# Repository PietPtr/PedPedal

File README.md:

# Footswitches

A modular USB MIDI footswitch controller. Each module is one PCB with a footswitch and an RGB
LED, and modules chain together with ribbon cables. The first module carries a Raspberry Pi
Pico, which is the USB MIDI device. All parts are through-hole. Firmware and host tools are in Rust.

- [docs/build.md](docs/build.md) ([PDF](docs/build.pdf)): build instructions
- [docs/design.md](docs/design.md): board and enclosure design
- [docs/bom.md](docs/bom.md): parts list
- [docs/firmware.md](docs/firmware.md): firmware, config libraries (Rust, Python, JS), the `fsctl` tool and the browser config page
- `pcb/`: KiCad project. `mech/`: plates, walls and 3D assembly. `firmware/`, `driver/`, `core/`: Rust code. `driver-py/`, `driver-js/`: Python and JS config libraries. `site/`: product page and config page.

--- 

Basically all of this is AI generated. Let's see if this thing actually works.

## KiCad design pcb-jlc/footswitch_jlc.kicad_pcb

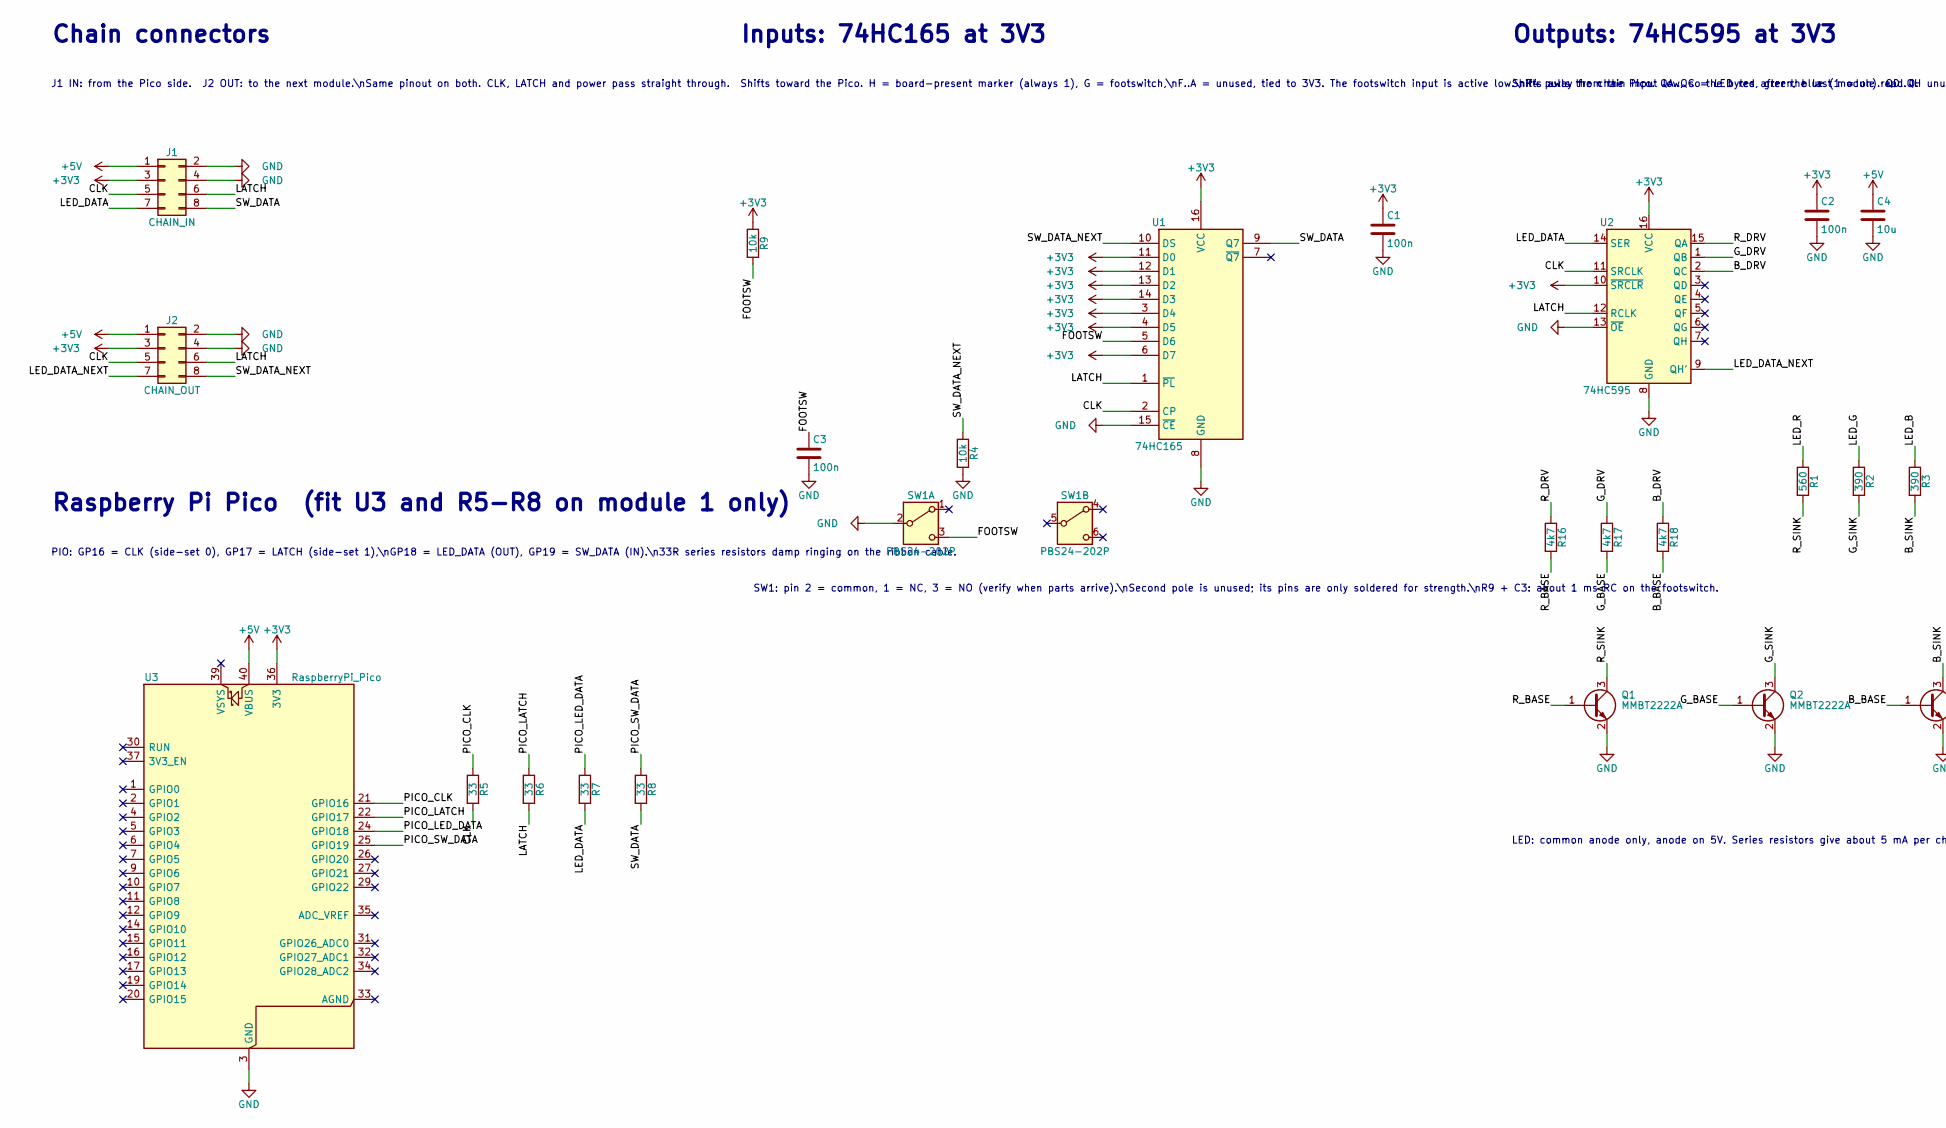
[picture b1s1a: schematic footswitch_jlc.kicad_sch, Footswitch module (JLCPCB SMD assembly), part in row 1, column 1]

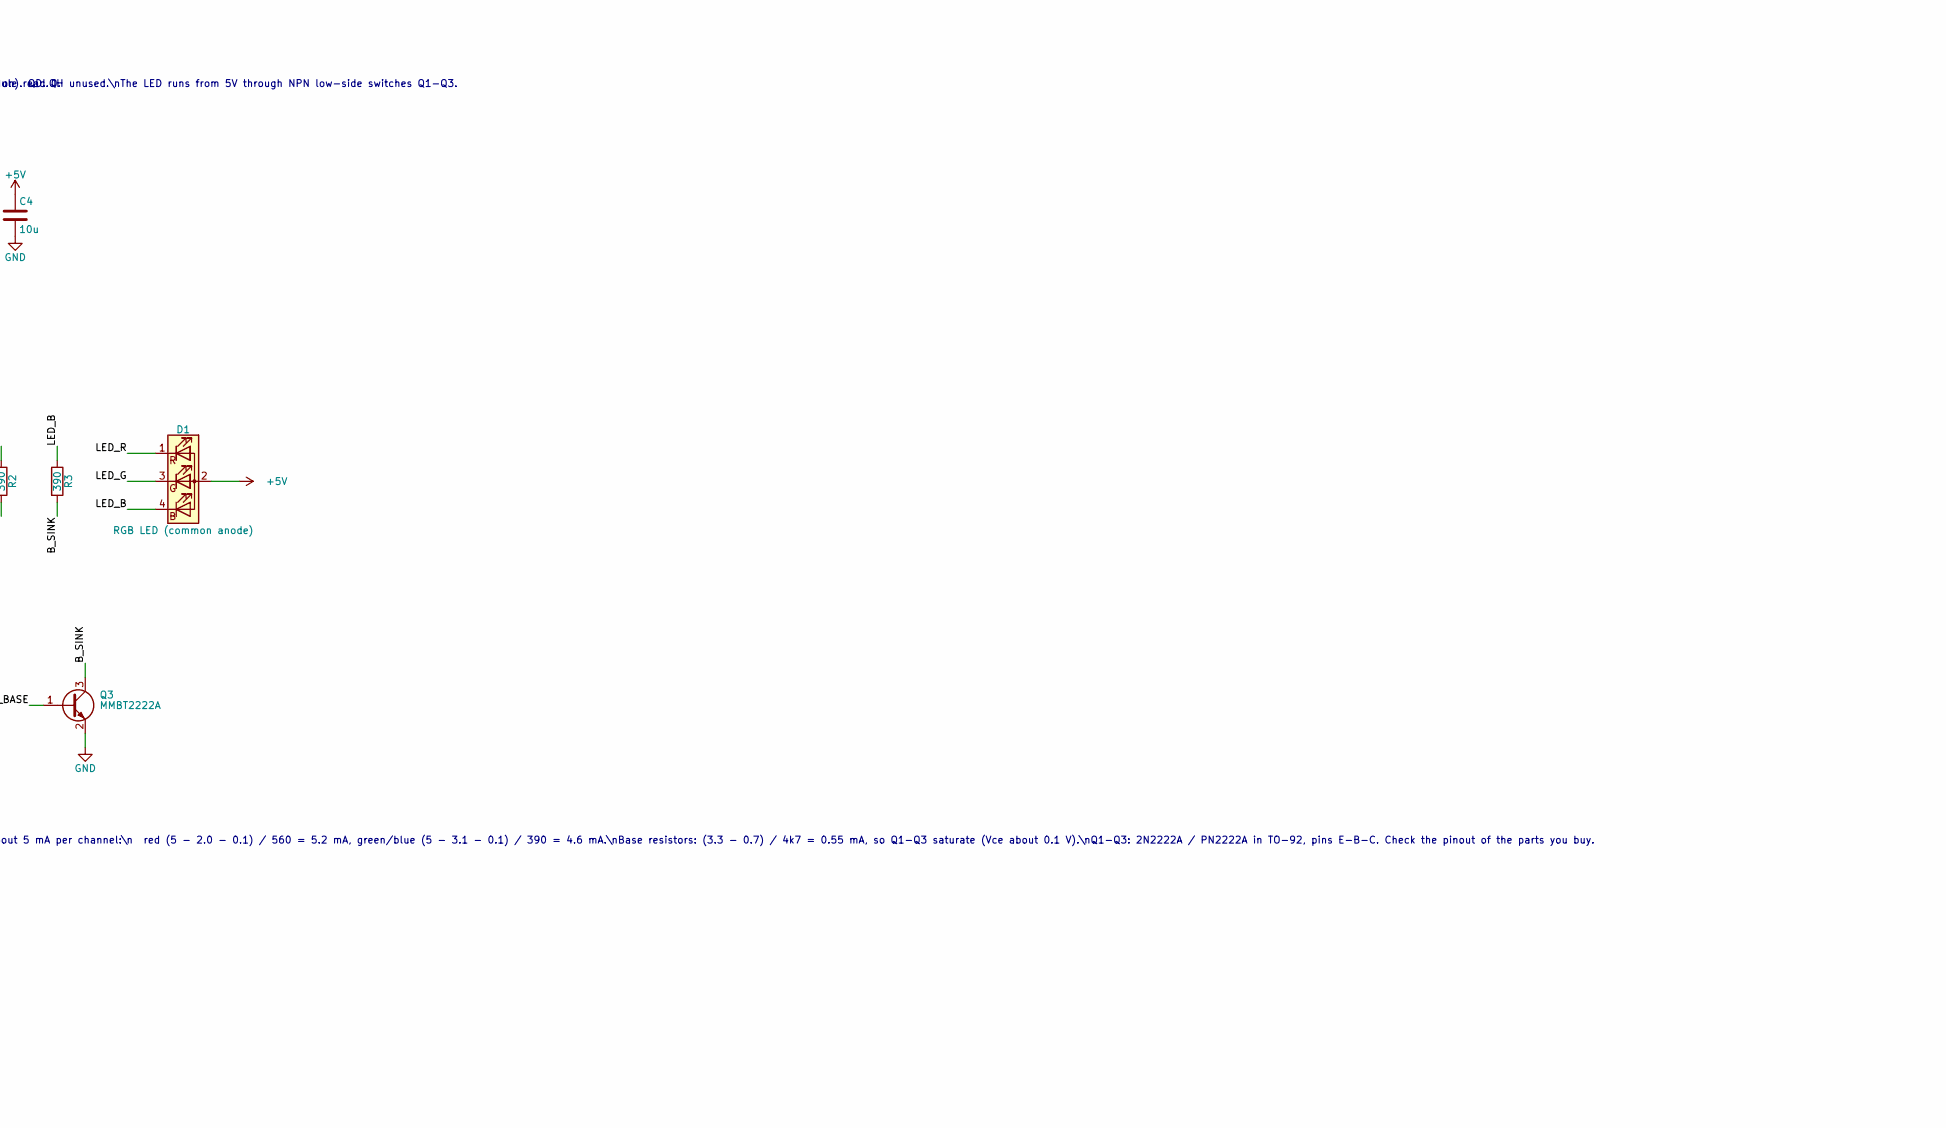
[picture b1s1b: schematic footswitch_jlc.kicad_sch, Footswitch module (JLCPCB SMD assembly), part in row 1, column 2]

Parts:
C1, C2, C3: 100n; C_0805_2012Metric; LCSC C49678
C4: 10u; C_0805_2012Metric; LCSC C15850
D1: RGB LED (common anode); LED_D5.0mm-4_RGB_Staggered_Pins
J1: CHAIN_IN; IDC-Header_2x04_P2.54mm_Vertical_SMD_JLC; LCSC C56143593
J2: CHAIN_OUT; IDC-Header_2x04_P2.54mm_Vertical_SMD_JLC; LCSC C56143593
Q1, Q2, Q3: MMBT2222A; SOT-23; LCSC C8512
R1: 560; R_0805_2012Metric; LCSC C28636
R2, R3: 390; R_0805_2012Metric; LCSC C17655
R4, R9: 10k; R_0805_2012Metric; LCSC C17414
R5, R6, R7, R8: 33; R_0805_2012Metric; LCSC C17634
R16, R17, R18: 4k7; R_0805_2012Metric; LCSC C17673
SW1: PBS24-202P
U1: 74HC165; SOIC-16_3.9x9.9mm_P1.27mm; LCSC C5613
U2: 74HC595; SOIC-16_3.9x9.9mm_P1.27mm; LCSC C5947
U3: RaspberryPi_Pico; RaspberryPi_Pico_Common_THT

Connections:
+3V3: C1.1, C2.1, J1.3, J2.3, R9.1, U1.3 (D4), U1.4 (D5), U1.6 (D7), U1.11 (D0), U1.12 (D1), U1.13 (D2), U1.14 (D3), U1.16 (VCC), U2.10 (~SRCLR), U2.16 (VCC), U3.36 (3V3)
+5V: C4.1, D1.2 (A), J1.1, J2.1, U3.40 (VBUS)
/B_BASE: Q3.1 (B), R18.2
/B_DRV: R18.1, U2.2 (QC)
/B_SINK: Q3.3 (C), R3.2
/CLK: J1.5, J2.5, R5.2, U1.2 (CP), U2.11 (SRCLK)
/FOOTSW: C3.1, R9.2, SW1.3 (C), U1.5 (D6)
/G_BASE: Q2.1 (B), R17.2
/G_DRV: R17.1, U2.1 (QB)
/G_SINK: Q2.3 (C), R2.2
/LATCH: J1.6, J2.6, R6.2, U1.1 (~PL), U2.12 (RCLK)
/LED_B: D1.4 (BK), R3.1
/LED_DATA: J1.7, R7.2, U2.14 (SER)
/LED_DATA_NEXT: J2.7, U2.9 (QH')
/LED_G: D1.3 (GK), R2.1
/LED_R: D1.1 (RK), R1.1
/PICO_CLK: R5.1, U3.21 (GPIO16)
/PICO_LATCH: R6.1, U3.22 (GPIO17)
/PICO_LED_DATA: R7.1, U3.24 (GPIO18)
/PICO_SW_DATA: R8.1, U3.25 (GPIO19)
/R_BASE: Q1.1 (B), R16.2
/R_DRV: R16.1, U2.15 (QA)
/R_SINK: Q1.3 (C), R1.2
/SW_DATA: J1.8, R8.2, U1.9 (Q7)
/SW_DATA_NEXT: J2.8, R4.1, U1.10 (DS)
GND: C1.2, C2.2, C3.2, C4.2, J1.2, J1.4, J2.2, J2.4, Q1.2 (E), Q2.2 (E), Q3.2 (E), R4.2, SW1.2 (B), U1.8 (GND), U1.15 (~CE), U2.8 (GND), U2.13 (~OE), U3.3 (GND), U3.8 (GND), U3.13 (GND), U3.18 (GND), U3.23 (GND), U3.28 (GND), U3.38 (GND)

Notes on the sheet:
Chain connectors
J1 IN: from the Pico side. J2 OUT: to the next module.\nSame pinout on both. CLK, LATCH and power pass straight through.
Raspberry Pi Pico (fit U3 and R5-R8 on module 1 only)
PIO: GP16 = CLK (side-set 0), GP17 = LATCH (side-set 1),\nGP18 = LED_DATA (OUT), GP19 = SW_DATA (IN).\n33R series resistors damp ringing on the ribbon cable.
Inputs: 74HC165 at 3V3
Shifts toward the Pico. H = board-present marker (always 1), G = footswitch,\nF..A = unused, tied to 3V3. The footswitch input is active low.\nR4 pulls the chain input low, so the bytes after the last module read 0.
SW1: pin 2 = common, 1 = NC, 3 = NO (verify when parts arrive).\nSecond pole is unused; its pins are only soldered for strength.\nR9 + C3: about 1 ms RC on the footswitch.
Outputs: 74HC595 at 3V3
Shifts away from the Pico. QA..QC = LED red, green, blue (1 = on). QD..QH unused.\nThe LED runs from 5V through NPN low-side switches Q1-Q3.
LED: common anode only, anode on 5V. Series resistors give about 5 mA per channel:\n red (5 - 2.0 - 0.1) / 560 = 5.2 mA, green/blue (5 - 3.1 - 0.1) / 390 = 4.6 mA.\nBase resistors: (3.3 - 0.7) / 4k7 = 0.55 mA, so Q1-Q3 saturate (Vce about 0.1 V).\nQ1-Q3: 2N2222A / PN2222A in TO-92, pins E-B-C. Chec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

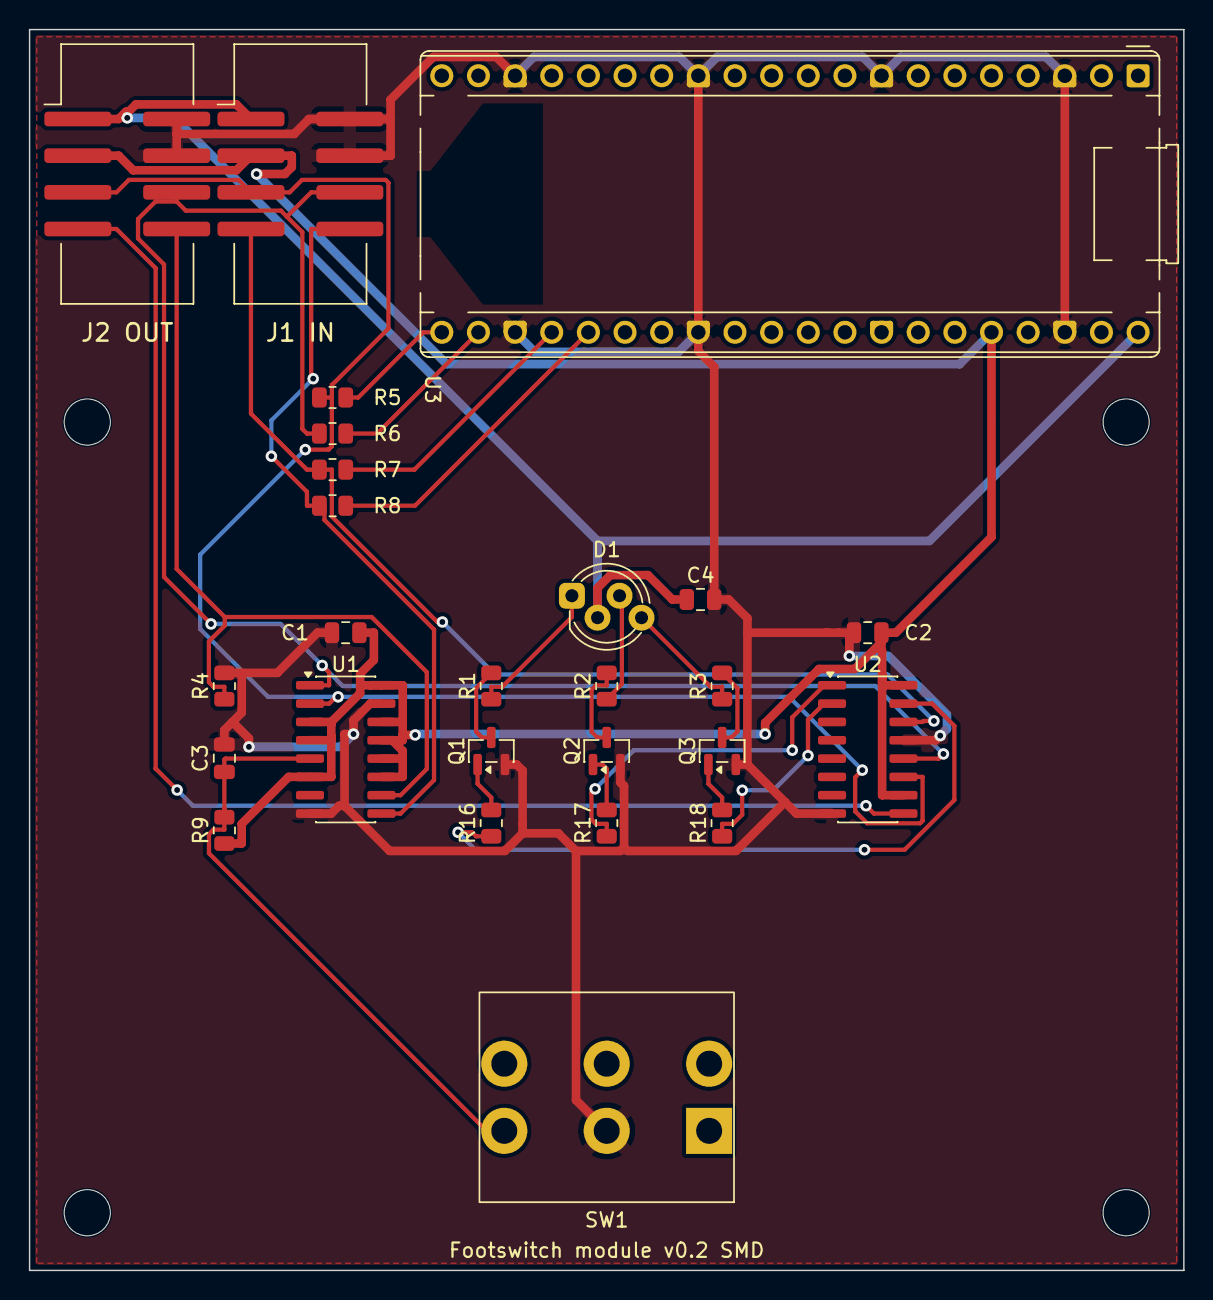
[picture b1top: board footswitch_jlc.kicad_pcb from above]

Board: 2 copper layers, 80.0 x 86.0 mm, 30 parts (0 on the bottom side), 26 nets.

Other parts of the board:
H1, H2, H3, H4: M3; MountingHole_3.2mm_M3

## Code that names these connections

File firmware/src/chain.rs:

//! Scans the module chain (74HC165 switch inputs, 74HC595 LED outputs) with PIO0.
//!
//! See docs/design.md, "Shift register bit assignment" and "Scan timing". One scan:
//!
//! 1. LATCH low: every 165 loads its inputs.
//! 2. LATCH high: every 595 copies what was shifted in during the previous scan to its outputs.
//! 3. 8 × MAX_PEDALS times: set LED_DATA, sample SW_DATA, pulse CLK high.
//!
//! The firmware always clocks MAX_PEDALS bytes, whatever the number of modules. Switch bytes
//! after the last module read 0 (the end-of-chain pull-down), which is how the module count is
//! found. LED bytes go out last module first, so the final bytes sent are the ones that stay in
//! the chain: whatever the chain length, module k ends up holding `leds[k]`.

use footswitch_core::MAX_PEDALS;
use rp2040_hal::gpio::{FunctionPio0, Pin, PullDown, PullNone, bank0};
use rp2040_hal::pac::{PIO0, RESETS};
use rp2040_hal::pio::{PIOBuilder, PIOExt, PinDir, Rx, SM0, ShiftDirection, Tx};

pub type ClkPin = Pin<bank0::Gpio16, FunctionPio0, PullNone>;
pub type LatchPin = Pin<bank0::Gpio17, FunctionPio0, PullNone>;
pub type LedDataPin = Pin<bank0::Gpio18, FunctionPio0, PullNone>;
pub type SwDataPin = Pin<bank0::Gpio19, FunctionPio0, PullDown>;

const CLK: u8 = 16; // side-set bit 0
const LATCH: u8 = 17; // side-set bit 1
const LED_DATA: u8 = 18; // OUT pin
const SW_DATA: u8 = 19; // IN pin

pub struct Chain {
    tx: Tx<(PIO0, SM0)>,
    rx: Rx<(PIO0, SM0)>,
    _pins: (ClkPin, LatchPin, LedDataPin, SwDataPin),
}

impl Chain {
    pub fn new(
        pio0: PIO0,
        resets: &mut RESETS,
        pins: (ClkPin, LatchPin, LedDataPin, SwDataPin),
    ) -> Self {
        // Side-set bits: 0 = CLK, 1 = LATCH. LATCH idles high, CLK idles low.
        // TX FIFO: first the byte count minus one, then one LED byte per word (in bits 31..24).
        // RX FIFO: one switch byte per word (bits 7..0, the first bit read in bit 7).
        let program = pio_proc::pio_asm!(
            ".side_set 2",
            ".wrap_target",
            "    pull block          side 0b10",     // byte count - 1
            "    mov y, osr          side 0b10",
            "    nop                 side 0b00 [7]", // LATCH low: 165s load
            "    nop                 side 0b10 [7]", // LATCH high: 595s update
            "byteloop:",
            "    pull block          side 0b10",     // next LED byte
            "    set x, 7            side 0b10",
            "bitloop:",
            "    out pins, 1         side 0b10 [1]", // LED_DATA
            "    in pins, 1          side 0b10 [1]", // sample SW_DATA
            "    jmp x-- bitloop     side 0b11 [2]", // CLK high: both chains shift
            "    push block          side 0b10",
            "    jmp y-- byteloop    side 0b10",
            ".wrap",
        );

        let (mut pio, sm0, _, _, _) = pio0.split(resets);
        let installed = pio.install(&program.program).unwrap();
        // 125 MHz / 31.25 = 4 MHz PIO clock. A bit takes 7 PIO cycles, so CLK runs at about
        // 570 kHz: slow, for margin on long ribbon chains. 16 modules scan in about 250 µs.
        let (mut sm, rx, tx) = PIOBuilder::from_installed_program(installed)
            .side_set_pin_base(CLK)
            .out_pins(LED_DATA, 1)
            .in_pin_base(SW_DATA)
            .out_shift_direction(ShiftDirection::Left)
            .in_shift_direction(ShiftDirection::Left)
            .autopull(false)
            .autopush(false)
            .clock_divisor_fixed_point(31, 64)
            .build(sm0);
        sm.set_pindirs([
            (CLK, PinDir::Output),
            (LATCH, PinDir::Output),
            (LED_DATA, PinDir::Output),
            (SW_DATA, PinDir::Input),
        ]);
        sm.start();
        // Dropping `pio` here is fine: the state machine and its program keep running.

        Chain { tx, rx, _pins: pins }
    }

    /// Runs one scan: shows `leds` (module 1 first; bit 0 red, 1 green, 2 blue) after the next
    /// latch, and returns the switch bytes read (module 1 first).
    ///
    /// LEDs lag one scan behind: the 595s latch the data at the start of the next scan.
    pub fn scan(&mut self, leds: &[u8; MAX_PEDALS]) -> [u8; MAX_PEDALS] {
        let mut switches = [0u8; MAX_PEDALS];
        while !self.tx.write((MAX_PEDALS - 1) as u32) {}
        let (mut sent, mut got) = (0, 0);
        while got < MAX_PEDALS {
            if sent < MAX_PEDALS && self.tx.write((leds[MAX_PEDALS - 1 - sent] as u32) << 24) {
                sent += 1;
            }
            if let Some(w) = self.rx.read() {
                switches[got] = w as u8;
                got += 1;
            }
        }
        switches
    }
}
